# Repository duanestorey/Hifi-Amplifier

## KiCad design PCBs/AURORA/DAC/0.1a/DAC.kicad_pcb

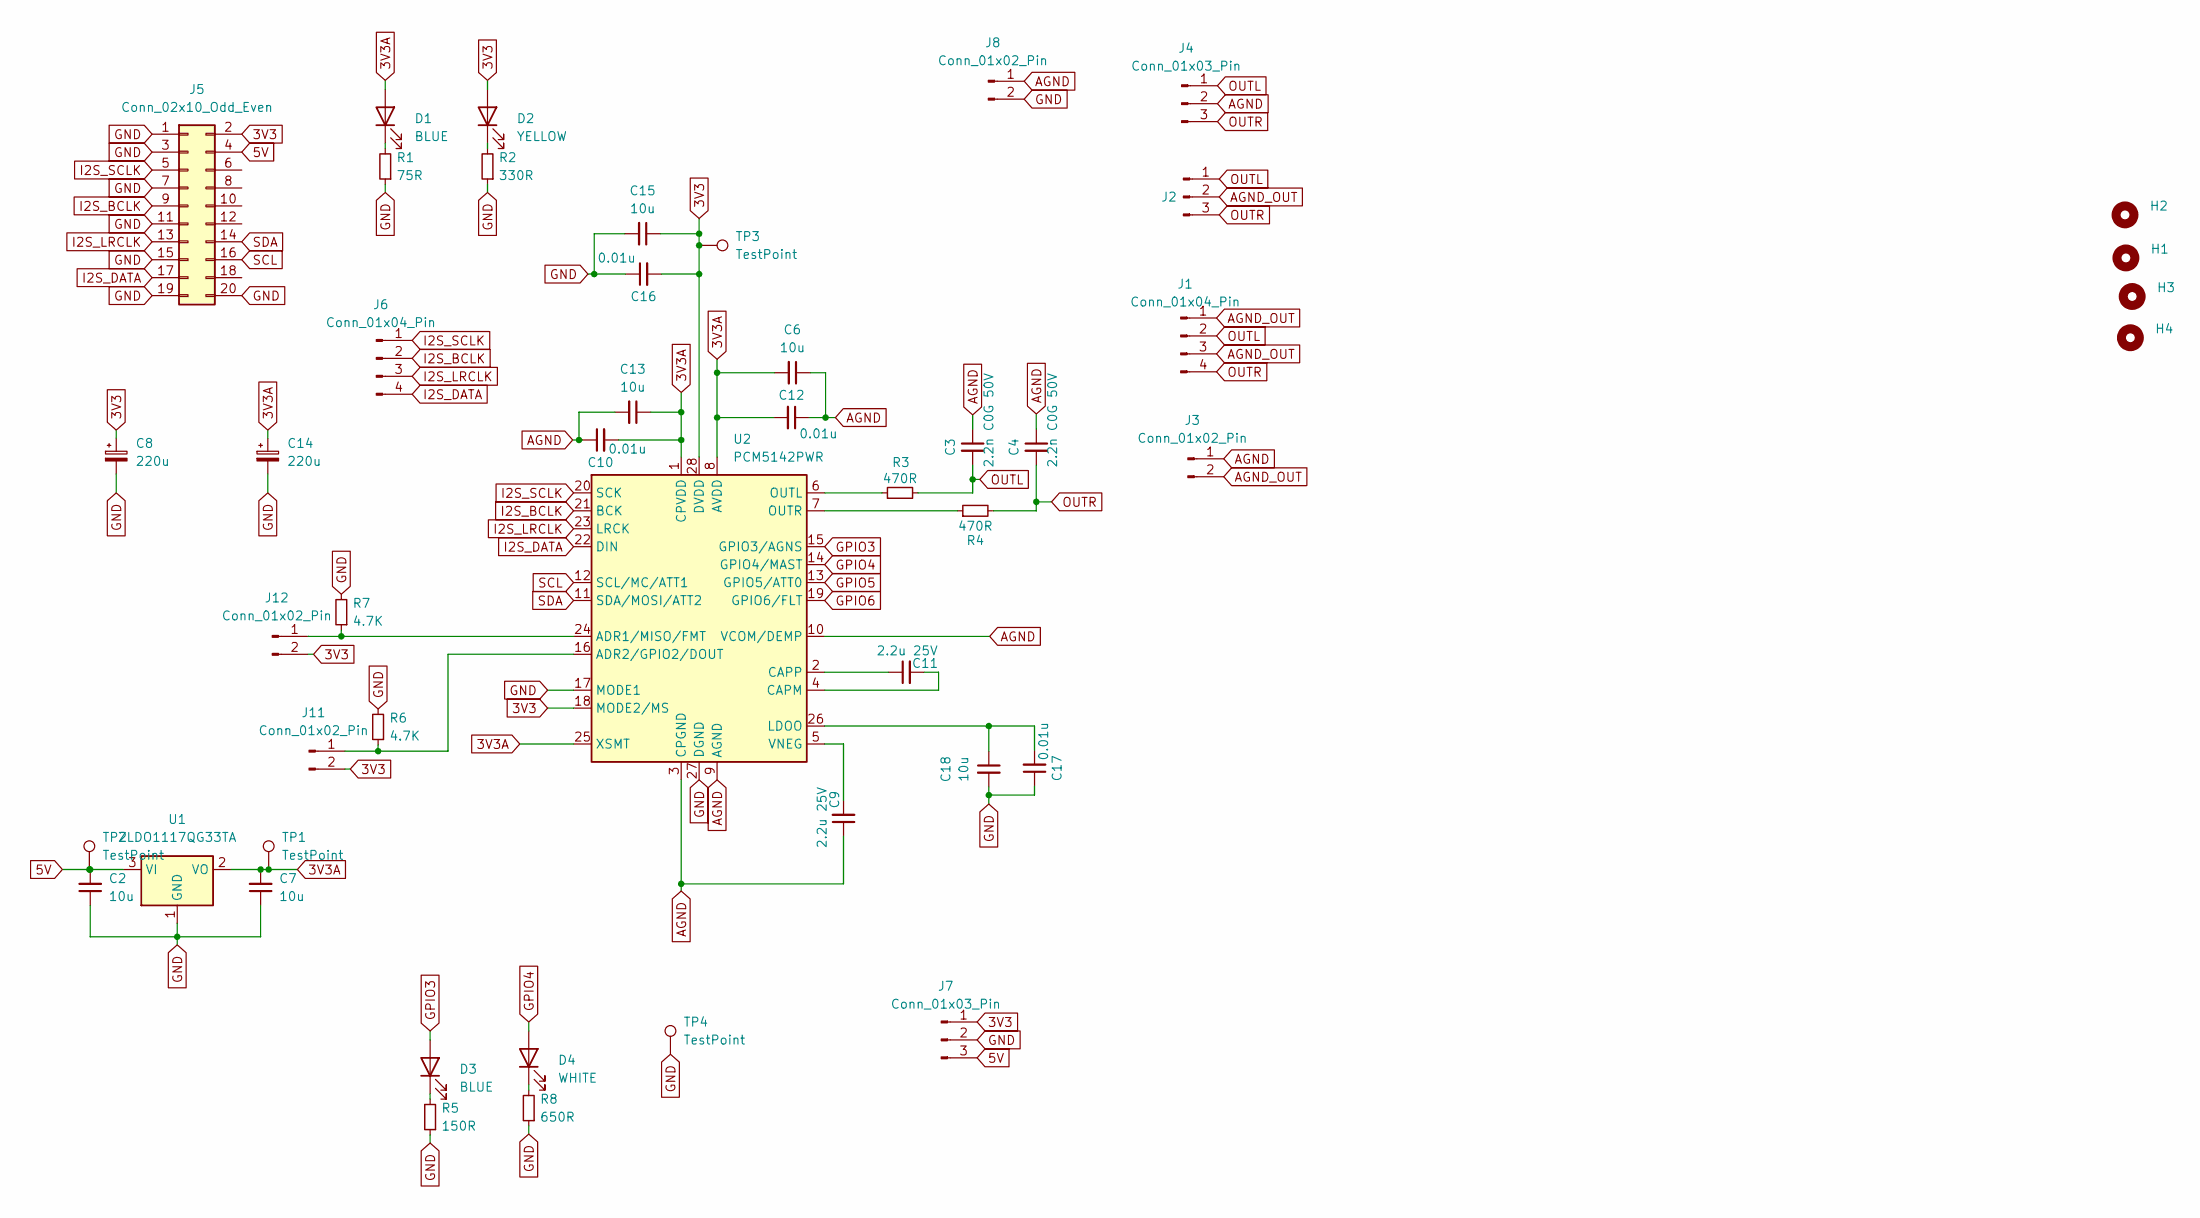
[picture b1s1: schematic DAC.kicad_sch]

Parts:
C2, C6, C7, C13, C15, C18: 10u; C_1206_3216Metric_Pad1.33x1.80mm_HandSolder
C3, C4: 2.2n C0G 50V; C_Rect_L4.6mm_W3.0mm_P2.50mm_MKS02_FKP02
C8, C14: 220u; CP_Radial_D6.3mm_P2.50mm
C9, C11: 2.2u 25V; C_0805_2012Metric
C10, C12, C16, C17: 0.01u; C_0805_2012Metric
D1, D3: BLUE; LED_0805_2012Metric_Pad1.15x1.40mm_HandSolder
D2: YELLOW; LED_0805_2012Metric_Pad1.15x1.40mm_HandSolder
D4: WHITE; LED_0805_2012Metric_Pad1.15x1.40mm_HandSolder
H1, H2, H3, H4: MountingHole; MountingHole_3.2mm_M3
J1: Conn_01x04_Pin; JST_PH_B4B-PH-K_1x04_P2.00mm_Vertical
J2, J7: Conn_01x03_Pin; JST_PH_B3B-PH-K_1x03_P2.00mm_Vertical
J3, J8, J11, J12: Conn_01x02_Pin; PinHeader_1x02_P2.54mm_Vertical
J4: Conn_01x03_Pin; PinHeader_1x03_P2.54mm_Vertical
J5: Conn_02x10_Odd_Even; PinHeader_2x10_P2.54mm_Vertical
J6: Conn_01x04_Pin; PinHeader_1x04_P2.54mm_Vertical
R1: 75R; R_0603_1608Metric_Pad0.98x0.95mm_HandSolder
R2: 330R; R_0603_1608Metric_Pad0.98x0.95mm_HandSolder
R3, R4: 470R; R_1206_3216Metric_Pad1.30x1.75mm_HandSolder
R5: 150R; R_0603_1608Metric_Pad0.98x0.95mm_HandSolder
R6, R7: 4.7K; R_0603_1608Metric_Pad0.98x0.95mm_HandSolder
R8: 650R; R_0603_1608Metric_Pad0.98x0.95mm_HandSolder
TP1, TP2, TP3, TP4: TestPoint; TestPoint_Pad_2.0x2.0mm
U1: ZLDO1117QG33TA; SOT-223-3_TabPin2
U2: PCM5142PWR; TSSOP-28_4.4x9.7mm_P0.65mm

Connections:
3V3: C8.1, C15.1, C16.2, D2.2 (A), J5.2, J7.1, J11.2, J12.2, TP3.1, U2.18 (MODE2/MS), U2.28 (DVDD)
3V3A: C6.2, C7.2, C10.2, C12.2, C13.1, C14.1, D1.2 (A), TP1.1, U1.2 (VO), U2.1 (CPVDD), U2.8 (AVDD), U2.25 (XSMT)
5V: C2.2, J5.4, J7.3, TP2.1, U1.3 (VI)
AGND: C3.1, C4.1, C6.1, C9.1, C10.1, C12.1, C13.2, J3.1, J4.2, J8.1, U2.3 (CPGND), U2.9 (AGND), U2.10 (VCOM/DEMP)
AGND_OUT: J1.1, J1.3, J2.2, J3.2
GND: C2.1, C7.1, C8.2, C14.2, C15.2, C16.1, C17.1, C18.2, J5.1, J5.3, J5.7, J5.11, J5.15, J5.19, J5.20, J7.2, J8.2, R1.1, R2.1, R5.1, R6.2, R7.2, R8.1, TP4.1, U1.1 (GND), U2.17 (MODE1), U2.27 (DGND)
GPIO3: D3.2 (A), U2.15 (GPIO3/AGNS)
GPIO4: D4.2 (A), U2.14 (GPIO4/MAST)
GPIO5: U2.13 (GPIO5/ATT0)
GPIO6: U2.19 (GPIO6/FLT)
I2S_BCLK: J5.9, J6.2, U2.21 (BCK)
I2S_DATA: J5.17, J6.4, U2.22 (DIN)
I2S_LRCLK: J5.13, J6.3, U2.23 (LRCK)
I2S_SCLK: J5.5, J6.1, U2.20 (SCK)
unnamed: D1.1 (K), R1.2
unnamed: D2.1 (K), R2.2
unnamed: D3.1 (K), R5.2
unnamed: D4.1 (K), R8.2
unnamed: J11.1, R6.1, U2.16 (ADR2/GPIO2/DOUT)
unnamed: J12.1, R7.1, U2.24 (ADR1/MISO/FMT)
unnamed: C11.2, U2.4 (CAPM)
unnamed: C11.1, U2.2 (CAPP)
unnamed: C17.2, C18.1, U2.26 (LDOO)
unnamed: R3.1, U2.6 (OUTL)
unnamed: R4.1, U2.7 (OUTR)
unnamed: C9.2, U2.5 (VNEG)
OUTL: C3.2, J1.2, J2.1, J4.1, R3.2
OUTR: C4.2, J1.4, J2.3, J4.3, R4.2
SCL: J5.16, U2.12 (SCL/MC/ATT1)
SDA: J5.14, U2.11 (SDA/MOSI/ATT2)

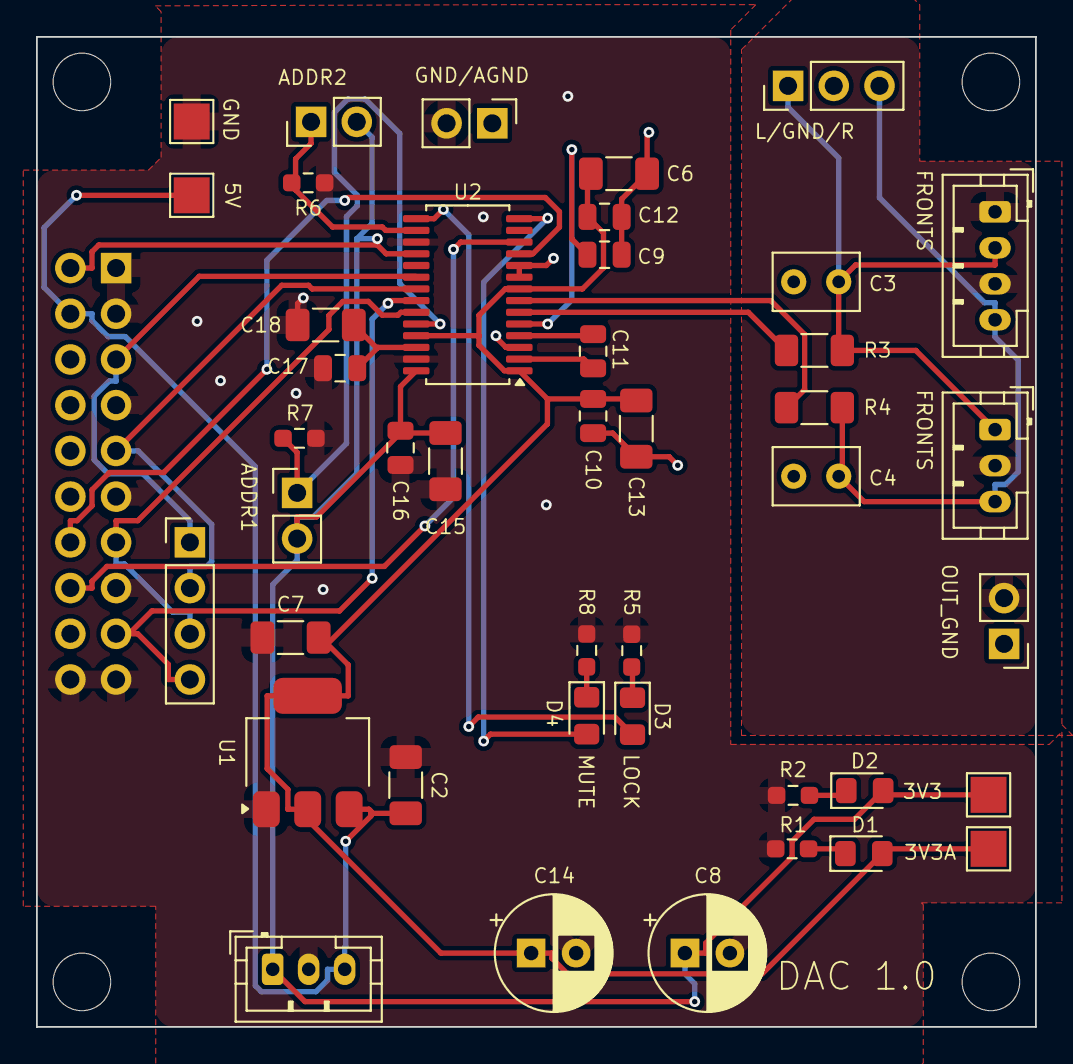
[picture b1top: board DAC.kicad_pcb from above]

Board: 4 copper layers, 55.5 x 55.0 mm, 48 parts (1 on the bottom side), 28 nets.

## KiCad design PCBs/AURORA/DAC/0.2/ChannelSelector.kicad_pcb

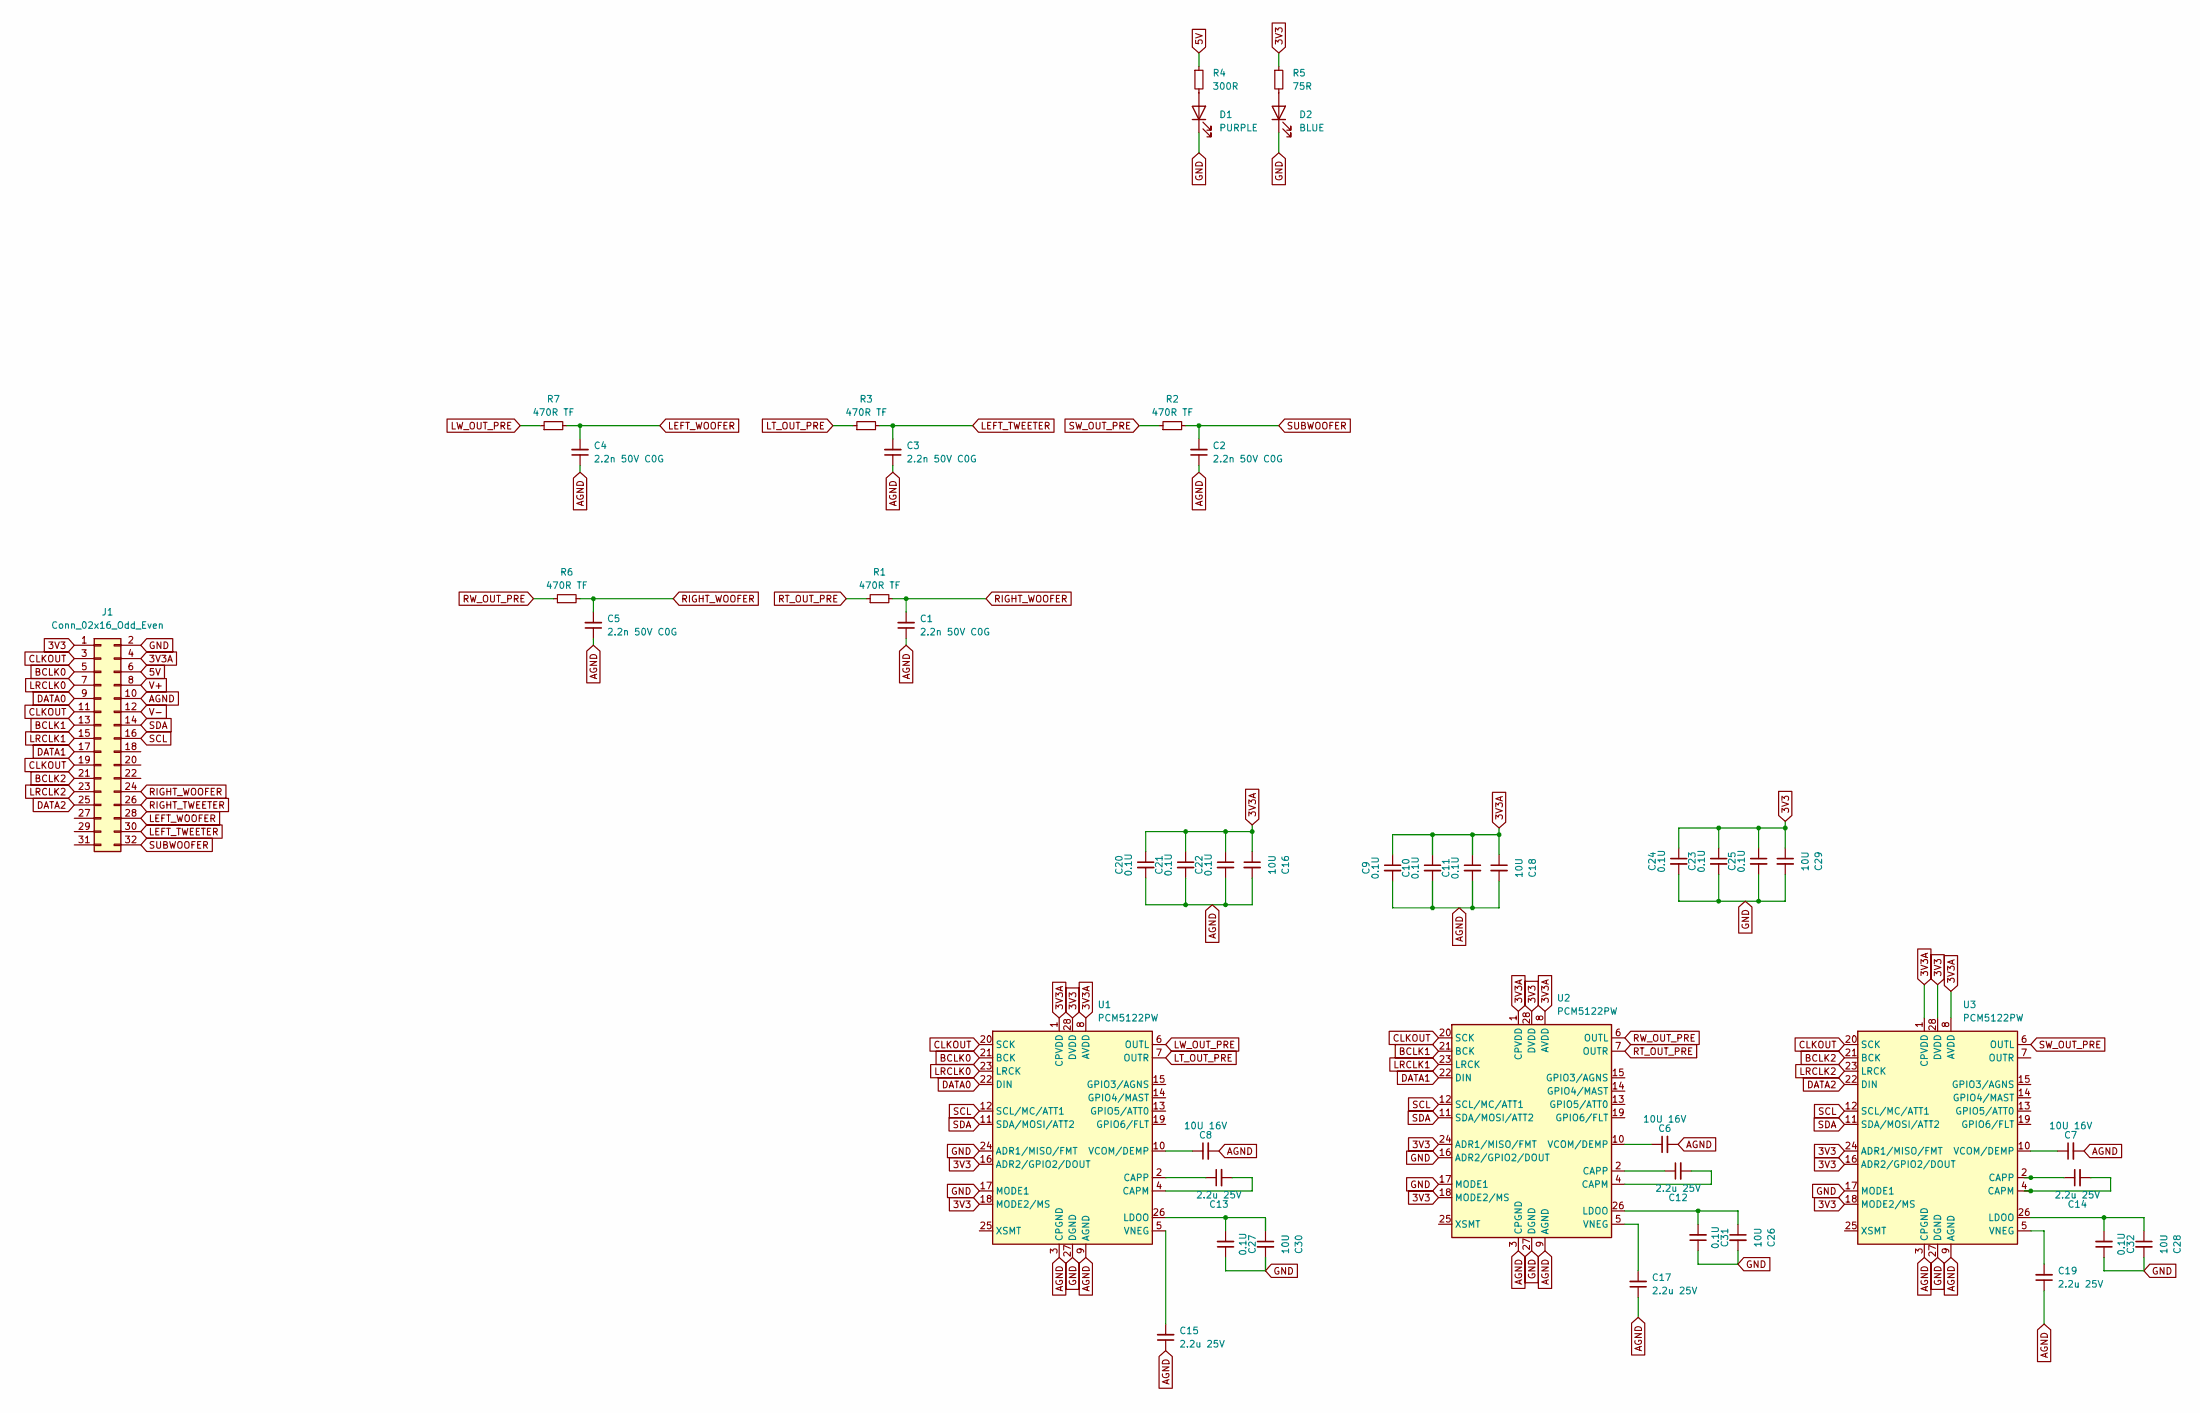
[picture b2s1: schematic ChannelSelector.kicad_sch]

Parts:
C1, C2, C3, C4, C5: 2.2n 50V C0G; C_0805_2012Metric_Pad1.18x1.45mm_HandSolder
C6, C7, C8: 10U 16V; C_0805_2012Metric_Pad1.18x1.45mm_HandSolder
C9, C10, C11, C20, C21, C22, C23, C24, C25, C27, C31, C32: 0.1U; C_0805_2012Metric_Pad1.18x1.45mm_HandSolder
C12, C13, C14: 2.2u 25V; C_0805_2012Metric_Pad1.18x1.45mm_HandSolder
C15, C17, C19: 2.2u 25V; C_1206_3216Metric_Pad1.33x1.80mm_HandSolder
C16, C18, C26, C28, C29, C30: 10U; C_1206_3216Metric_Pad1.33x1.80mm_HandSolder
D1: PURPLE; D_0805_2012Metric
D2: BLUE; D_0805_2012Metric
J1: Conn_02x16_Odd_Even; PinHeader_2x16_P2.54mm_Vertical
R1, R2, R3, R6, R7: 470R TF; C_0805_2012Metric_Pad1.18x1.45mm_HandSolder
R4: 300R; R_0603_1608Metric_Pad0.98x0.95mm_HandSolder
R5: 75R; R_0603_1608Metric_Pad0.98x0.95mm_HandSolder
U1, U2, U3: PCM5122PW; TSSOP-28_4.4x9.7mm_P0.65mm

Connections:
3V3: C23.1, C24.1, C25.1, C29.1, J1.1, R5.1, U1.16 (ADR2/GPIO2/DOUT), U1.18 (MODE2/MS), U1.28 (DVDD), U2.18 (MODE2/MS), U2.24 (ADR1/MISO/FMT), U2.28 (DVDD), U3.16 (ADR2/GPIO2/DOUT), U3.18 (MODE2/MS), U3.24 (ADR1/MISO/FMT), U3.28 (DVDD)
3V3A: C9.1, C10.1, C11.1, C16.1, C18.1, C20.1, C21.1, C22.1, J1.4, U1.1 (CPVDD), U1.8 (AVDD), U2.1 (CPVDD), U2.8 (AVDD), U3.1 (CPVDD), U3.8 (AVDD)
5V: J1.6, R4.1
AGND: C1.1, C2.1, C3.1, C4.1, C5.1, C6.2, C7.2, C8.2, C9.2, C10.2, C11.2, C15.1, C16.2, C17.1, C18.2, C19.1, C20.2, C21.2, C22.2, J1.10, U1.3 (CPGND), U1.9 (AGND), U2.3 (CPGND), U2.9 (AGND), U3.3 (CPGND), U3.9 (AGND)
BCLK0: J1.5, U1.21 (BCK)
BCLK1: J1.13, U2.21 (BCK)
BCLK2: J1.21, U3.21 (BCK)
CLKOUT: J1.3, J1.11, J1.19, U1.20 (SCK), U2.20 (SCK), U3.20 (SCK)
DATA0: J1.9, U1.22 (DIN)
DATA1: J1.17, U2.22 (DIN)
DATA2: J1.25, U3.22 (DIN)
GND: C23.2, C24.2, C25.2, C26.2, C27.1, C28.2, C29.2, C30.2, C31.1, C32.1, D1.1 (K), D2.1 (K), J1.2, U1.17 (MODE1), U1.24 (ADR1/MISO/FMT), U1.27 (DGND), U2.16 (ADR2/GPIO2/DOUT), U2.17 (MODE1), U2.27 (DGND), U3.17 (MODE1), U3.27 (DGND)
LEFT_TWEETER: C3.2, J1.30, R3.2
LEFT_WOOFER: C4.2, J1.28, R7.2
LRCLK0: J1.7, U1.23 (LRCK)
LRCLK1: J1.15, U2.23 (LRCK)
LRCLK2: J1.23, U3.23 (LRCK)
LT_OUT_PRE: R3.1, U1.7 (OUTR)
LW_OUT_PRE: R7.1, U1.6 (OUTL)
unnamed: D1.2 (A), R4.2
unnamed: D2.2 (A), R5.2
unnamed: C13.2, U1.4 (CAPM)
unnamed: C13.1, U1.2 (CAPP)
unnamed: C27.2, C30.1, U1.26 (LDOO)
unnamed: C8.1, U1.10 (VCOM/DEMP)
unnamed: C15.2, U1.5 (VNEG)
unnamed: C12.2, U2.4 (CAPM)
unnamed: C12.1, U2.2 (CAPP)
unnamed: C26.1, C31.2, U2.26 (LDOO)
unnamed: C6.1, U2.10 (VCOM/DEMP)
unnamed: C17.2, U2.5 (VNEG)
unnamed: C14.2, U3.4 (CAPM)
unnamed: C14.1, U3.2 (CAPP)
unnamed: C28.1, C32.2, U3.26 (LDOO)
unnamed: C7.1, U3.10 (VCOM/DEMP)
unnamed: C19.2, U3.5 (VNEG)
RIGHT_TWEETER: J1.26
RIGHT_WOOFER: C1.2, C5.2, J1.24, R1.2, R6.2
RT_OUT_PRE: R1.1, U2.7 (OUTR)
RW_OUT_PRE: R6.1, U2.6 (OUTL)
SCL: J1.16, U1.12 (SCL/MC/ATT1), U2.12 (SCL/MC/ATT1), U3.12 (SCL/MC/ATT1)
SDA: J1.14, U1.11 (SDA/MOSI/ATT2), U2.11 (SDA/MOSI/ATT2), U3.11 (SDA/MOSI/ATT2)
SUBWOOFER: C2.2, J1.32, R2.2
SW_OUT_PRE: R2.1, U3.6 (OUTL)
V+: J1.8
V-: J1.12

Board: 4 copper layers, 45 parts (0 on the bottom side), 43 nets, no tracks yet.

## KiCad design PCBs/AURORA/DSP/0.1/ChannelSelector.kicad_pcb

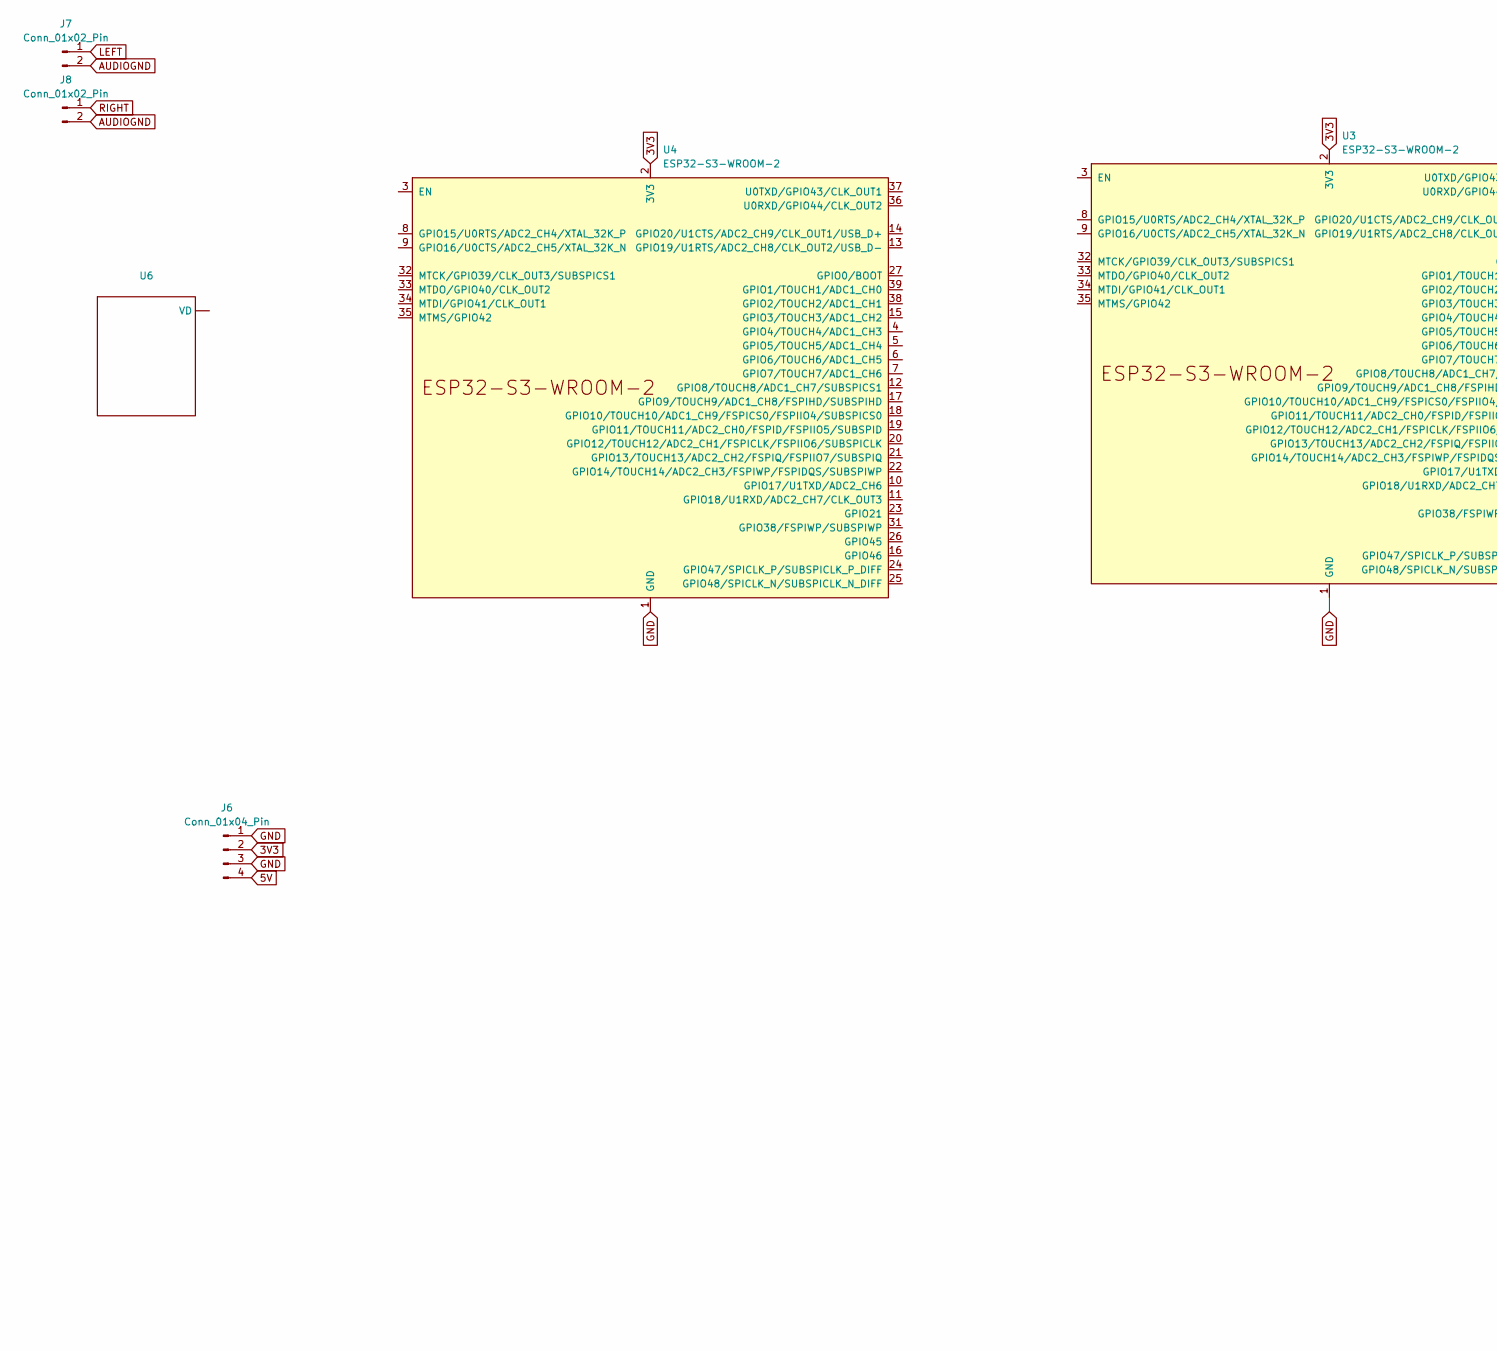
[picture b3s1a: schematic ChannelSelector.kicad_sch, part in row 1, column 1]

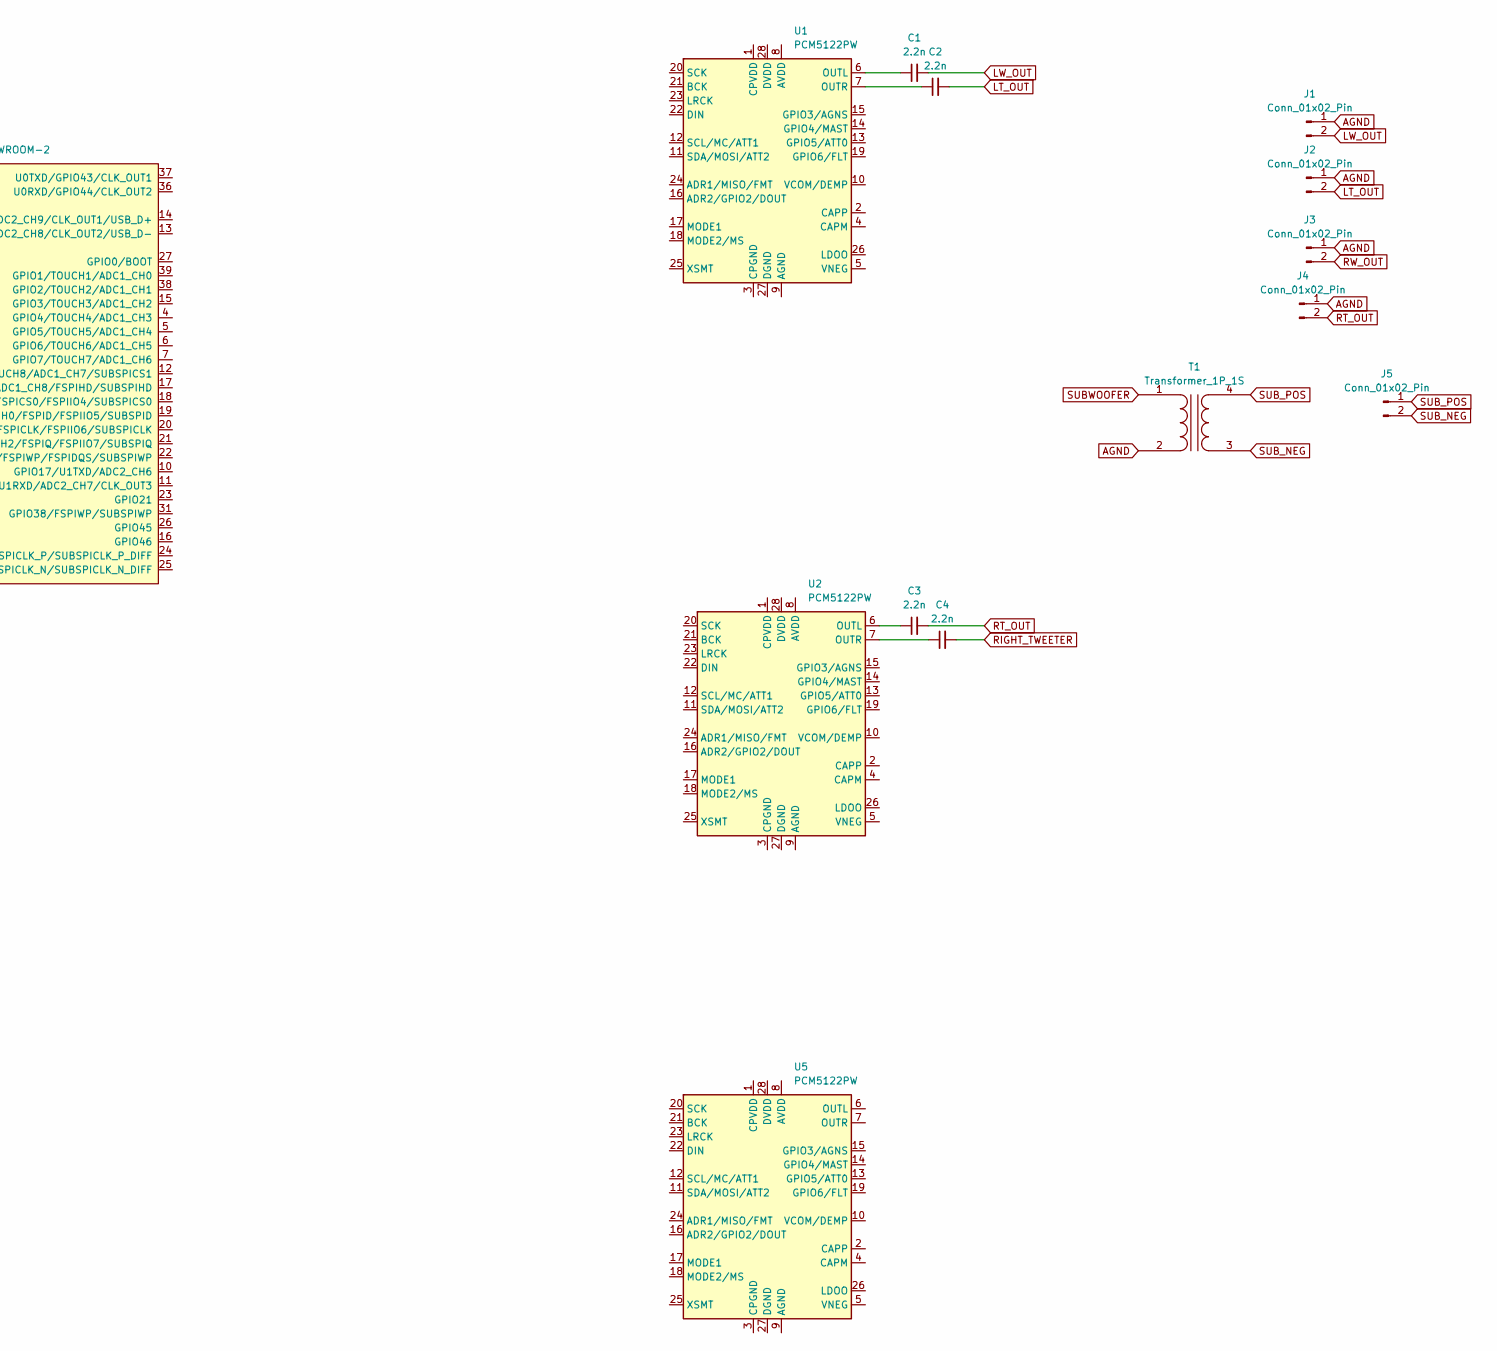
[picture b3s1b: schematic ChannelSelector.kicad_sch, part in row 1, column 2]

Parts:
C1, C2, C3, C4: 2.2n; C_Rect_L4.6mm_W3.0mm_P2.50mm_MKS02_FKP02
J1, J2, J3, J4, J5, J7, J8: Conn_01x02_Pin; JST_PH_B2B-PH-K_1x02_P2.00mm_Vertical
J6: Conn_01x04_Pin; JST_XH_B4B-XH-AM_1x04_P2.50mm_Vertical
T1: Transformer_1P_1S; DA101C
U1, U2, U5: PCM5122PW; TSSOP-28_4.4x9.7mm_P0.65mm
U3, U4: ESP32-S3-WROOM-2
U6: TSSOP-30_4.4x7.8mm_P0.5mm

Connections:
3V3: J6.2, U3.2 (3V3), U4.2 (3V3)
5V: J6.4
AGND: J1.1, J2.1, J3.1, J4.1, T1.2 (AB)
AUDIOGND: J7.2, J8.2
GND: J6.1, J6.3, U3.1 (GND), U3.40 (GND), U3.41 (GND), U4.1 (GND), U4.40 (GND), U4.41 (GND)
LEFT: J7.1
LT_OUT: C2.2, J2.2
LW_OUT: C1.2, J1.2
unnamed: C1.1, U1.6 (OUTL)
unnamed: C2.1, U1.7 (OUTR)
unnamed: C3.1, U2.6 (OUTL)
unnamed: C4.1, U2.7 (OUTR)
RIGHT: J8.1
RIGHT_TWEETER: C4.2
RT_OUT: C3.2, J4.2
RW_OUT: J3.2
SUBWOOFER: T1.1 (AA)
SUB_NEG: J5.2, T1.3 (SA)
SUB_POS: J5.1, T1.4 (SB)

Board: 4 copper layers, 18 parts (0 on the bottom side), 13 nets, no tracks yet.

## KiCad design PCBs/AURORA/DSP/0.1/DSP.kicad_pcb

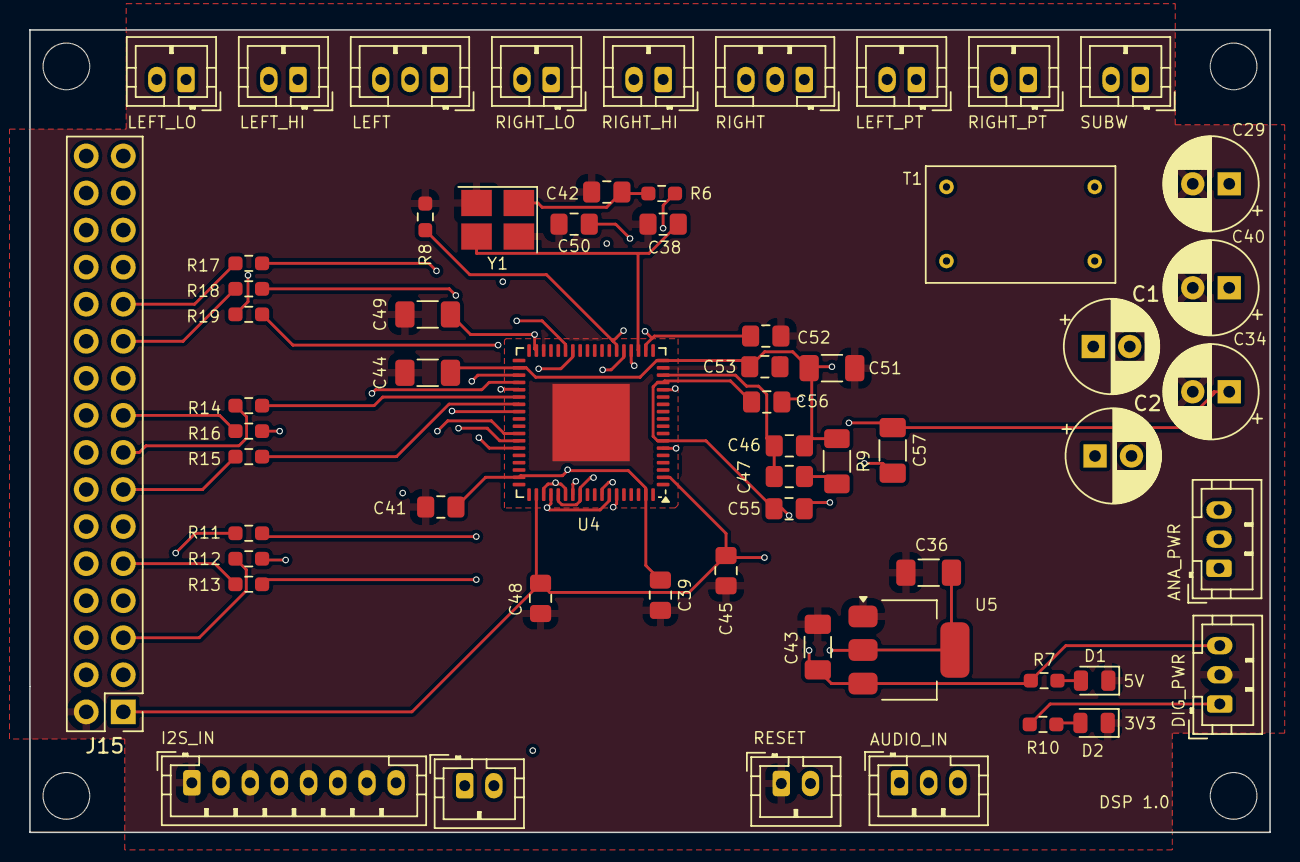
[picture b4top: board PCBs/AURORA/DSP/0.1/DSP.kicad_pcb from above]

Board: 4 copper layers, 85.0 x 55.0 mm, 64 parts (0 on the bottom side), 49 nets.

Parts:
C1, C2, C29, C34, C40: 220u; CP_Radial_D6.3mm_P2.50mm
C36, C43: 10u; C_1206_3216Metric_Pad1.33x1.80mm_HandSolder
C38, C42: 22p; C_0805_2012Metric_Pad1.18x1.45mm_HandSolder
C39, C41, C45, C48, C50, C52, C53, C55, C56: 0.1U; C_0805_2012Metric_Pad1.18x1.45mm_HandSolder
C44, C49, C51: 10U 10V; C_1206_3216Metric_Pad1.33x1.80mm_HandSolder
C46: 3.3N C0G; C_0805_2012Metric_Pad1.18x1.45mm_HandSolder
C47: 56N C0G; C_0805_2012Metric_Pad1.18x1.45mm_HandSolder
C57: 10U; C_1206_3216Metric_Pad1.33x1.80mm_HandSolder
D1: PURPLE; D_0805_2012Metric
D2: BLUE; D_0805_2012Metric
H1, H2, H3, H4: MountingHole; MountingHole_3.2mm_M3
J1, J2, J4, J5, J7, J8, J9, J13: Conn_01x02_Pin; JST_PH_B2B-PH-K_1x02_P2.00mm_Vertical
J3, J6, J10, J12, J16: Conn_01x03_Pin; JST_PH_B3B-PH-K_1x03_P2.00mm_Vertical
J11: Conn_01x02_Male; JST_PH_B2B-PH-K_1x02_P2.00mm_Vertical
J14: Conn_01x08_Pin; JST_PH_B8B-PH-K_1x08_P2.00mm_Vertical
J15: Conn_02x16_Odd_Even; PinHeader_2x16_P2.54mm_Vertical
R6: 100R; R_0603_1608Metric_Pad0.98x0.95mm_HandSolder
R7: 300R; R_0603_1608Metric_Pad0.98x0.95mm_HandSolder
R8: 4.7K; R_0603_1608Metric_Pad0.98x0.95mm_HandSolder
R9: 475R; R_1206_3216Metric_Pad1.30x1.75mm_HandSolder
R10: 75R; R_0603_1608Metric_Pad0.98x0.95mm_HandSolder
R11, R12, R13, R14, R15, R16, R17, R18, R19: 22R; R_0603_1608Metric_Pad0.98x0.95mm_HandSolder
T1: Transformer_1P_1S; DA101C
U4: ADAU1452; LFCSP-72-1EP_10x10mm_P0.5mm_EP5.3x5.3mm
U5: ZLDO1117QG33TA; SOT-223-3_TabPin2
Y1: 24.576Mhz; Crystal_SMD_3225-4Pin_3.2x2.5mm_HandSoldering

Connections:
1V2: C39.1, C41.1, C49.1, C50.1, C52.1, U4.20 (DVDD), U4.35 (DVDD), U4.53 (DVDD), U4.71 (DVDD)
3V3: C40.1, C44.1, C45.1, C46.2, C48.1, C51.1, C53.1, J10.1, J15.1, R9.1, R10.1, U4.2 (IOVDD), U4.18 (IOVDD), U4.38 (IOVDD), U4.56 (IOVDD)
3V3A: C34.1, C36.2, C55.1, C56.1, C57.1, J15.4, U4.7 (AVDD), U4.15 (PVDD), U5.2 (VO)
5V: C29.1, C43.2, J10.3, J15.6, R7.1, U5.3 (VI)
AGND: C1.2, C2.1, C55.2, C56.2, C57.2, J1.1, J2.1, J3.2, J4.1, J5.1, J6.2, J7.1, J8.1, J12.2, J15.10, J16.2, T1.2 (AB), U4.6 (AGND), U4.14 (PGND)
BCLK0: J15.5, R12.1
BCLK1: J15.13, R15.1
BCLK2: J15.21, R18.1
BCLK_IN: J14.4, U4.57 (BCLK_IN0), U4.60 (BCLK_IN1), U4.65 (BCLK_IN2)
CLKOUT: J15.3, J15.11, J15.19, U4.23 (CLKOUT)
DATA0: J15.9, R13.1
DATA1: J15.17, R16.1
DATA2: J15.25, R19.1
DATA_IN: J14.8, U4.59 (SDATA_IN0), U4.62 (SDATA_IN1), U4.67 (SDATA_IN2)
GND: C29.2, C34.2, C36.1, C38.2, C39.2, C40.2, C41.2, C42.2, C43.1, C44.2, C45.2, C48.2, C49.2, C50.2, C51.2, C52.2, C53.2, D1.1 (K), D2.1 (K), J10.2, J13.1, J14.1, J14.3, J14.5, J14.7, J15.2, R8.1, U4.1 (DGND), U4.17 (DGND), U4.19 (DGND), U4.25 (DGND), U4.34 (SELFBOOT), U4.36 (DGND), U4.37 (DGND), U4.54 (DGND), U4.55 (DGND), U4.72 (DGND), U5.1 (GND), Y1.2, Y1.4
LEFT_IN: J7.2, J12.1
LEFT_TWEETER: J2.2, J3.3, J15.30
LEFT_WOOFER: J1.2, J3.1, J15.28
LRCLK0: J15.7, R11.1
LRCLK1: J15.15, R14.1
LRCLK2: J15.23, R17.1
LRCLK_IN: J14.6, U4.58 (LRCLK_IN0/MP10), U4.61 (LRCLK_IN1/MP11), U4.66 (LRCLK_IN2/MP12)
unnamed: C42.1, R6.2, Y1.1
unnamed: C47.2, R9.2
unnamed: D1.2 (A), R7.2
unnamed: D2.2 (A), R10.2
unnamed: R12.2, U4.40 (BCLK_OUT0)
unnamed: R15.2, U4.43 (BCLK_OUT1)
unnamed: R18.2, U4.48 (BCLK_OUT2)
unnamed: R11.2, U4.39 (LRCLK_OUT0/MP4)
unnamed: R14.2, U4.42 (LRCLK_OUT1/MP5)
unnamed: R17.2, U4.47 (LRCLK_OUT2/MP8)
unnamed: R13.2, U4.41 (SDATA_OUT0)
unnamed: R16.2, U4.44 (SDATA_OUT1)
unnamed: R19.2, U4.49 (SDATA_OUT2)
unnamed: C38.1, U4.21 (XTALIN/MCLK), Y1.3
unnamed: R6.1, U4.22 (XTALOUT)
PLL_LF: C46.1, C47.1, U4.16 (PLLFILT)
RESET: J13.2, R8.2, U4.24 (~RESET)
RIGHT_IN: J8.2, J12.3
RIGHT_TWEETER: J5.2, J6.3, J15.26
RIGHT_WOOFER: J4.2, J6.1, J15.24
SCL: J11.1, J15.16, U4.31 (SCLK/SCL)
SDA: J11.2, J15.14, U4.30 (MISO/SDA)
SUBWOOFER: J15.32, T1.1 (AA)
SUBW_NEG: J9.1, T1.3 (SA)
SUBW_POS: J9.2, T1.4 (SB)
V+: C1.1, J15.8, J16.3
V-: C2.2, J15.12, J16.1

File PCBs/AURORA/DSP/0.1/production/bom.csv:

Designator,Footprint,Quantity,Value,LCSC Part #
"C1, C2, C29, C34, C40",CP_Radial_D6.3mm_P2.50mm,5,220u,
"C36, C43, C57",1206,3,10u,
"C38, C42",0805,2,22p,
"C39, C41, C45, C48, C50, C52, C53, C55, C56",0805,9,0.1U,
"C44, C49, C51",1206,3,10U 10V,
C46,0805,1,3.3N C0G,
C47,0805,1,56N C0G,
D1,0805,1,PURPLE,
D2,0805,1,BLUE,
"J1, J13, J2, J4, J5, J7, J8, J9",JST_PH_B2B-PH-K_1x02_P2.00mm_Vertical,8,Conn_01x02_Pin,
"J10, J12, J16, J3, J6",JST_PH_B3B-PH-K_1x03_P2.00mm_Vertical,5,Conn_01x03_Pin,
J11,JST_PH_B2B-PH-K_1x02_P2.00mm_Vertical,1,Conn_01x02_Male,
J14,JST_PH_B8B-PH-K_1x08_P2.00mm_Vertical,1,Conn_01x08_Pin,
J15,PinHeader_2x16_P2.54mm_Vertical,1,Conn_02x16_Odd_Even,
R10,0603,1,75R,
"R11, R12, R13, R14, R15, R16, R17, R18, R19",0603,9,22R,
R6,0603,1,100R,
R7,0603,1,300R,
R8,0603,1,4.7K,
R9,1206,1,475R,
T1,DA101C,1,Transformer_1P_1S,
U4,LFCSP-72-1EP_10x10mm_P0.5mm_EP5.3x5.3mm,1,ADAU1452,
U5,SOT-223-3_TabPin2,1,ZLDO1117QG33TA,
Y1,Crystal_SMD_3225-4Pin_3.2x2.5mm_HandSoldering,1,24.576Mhz,
